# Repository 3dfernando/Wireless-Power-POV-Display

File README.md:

# Wireless-Power-POV-Display
This project was designed as a hobby acivity by a Mechanical Engineer. Therefore, it probably has a lot of problems from the Electrical Engineering point of view. If you think you can improve this project, please branch this Git and comment!

The project consists of a POV (Persistence of Vision) display that, unlike most of the POV displays found in the internet, is not powered by a battery but by the mains power. The regular battery-powered design is a simple solution to the problem of supplying the power needed to light up the LEDs and power the processor [Which are spinning], by making the battery also spin. 

Although the solution is effective, it's a hassle to be applied for a decorative item, for example, as one needs to stop and access the device from time to time to recharge the battery. Normally decorative objects have a no-maintenance requirement (which in some cases might be extremely difficult to achieve!).

The next easiest way of avoiding this problem is through a brushed connection. This is also possible, although it might be a little bit too noisy for a decorative device - and still would be hard for a DIY setup to require no maintenance after some hours of operation. So I thought a wireless power transfer system would be a perfect solution! So why not try it out and in the middle of the path learn more about wireless power transfer?

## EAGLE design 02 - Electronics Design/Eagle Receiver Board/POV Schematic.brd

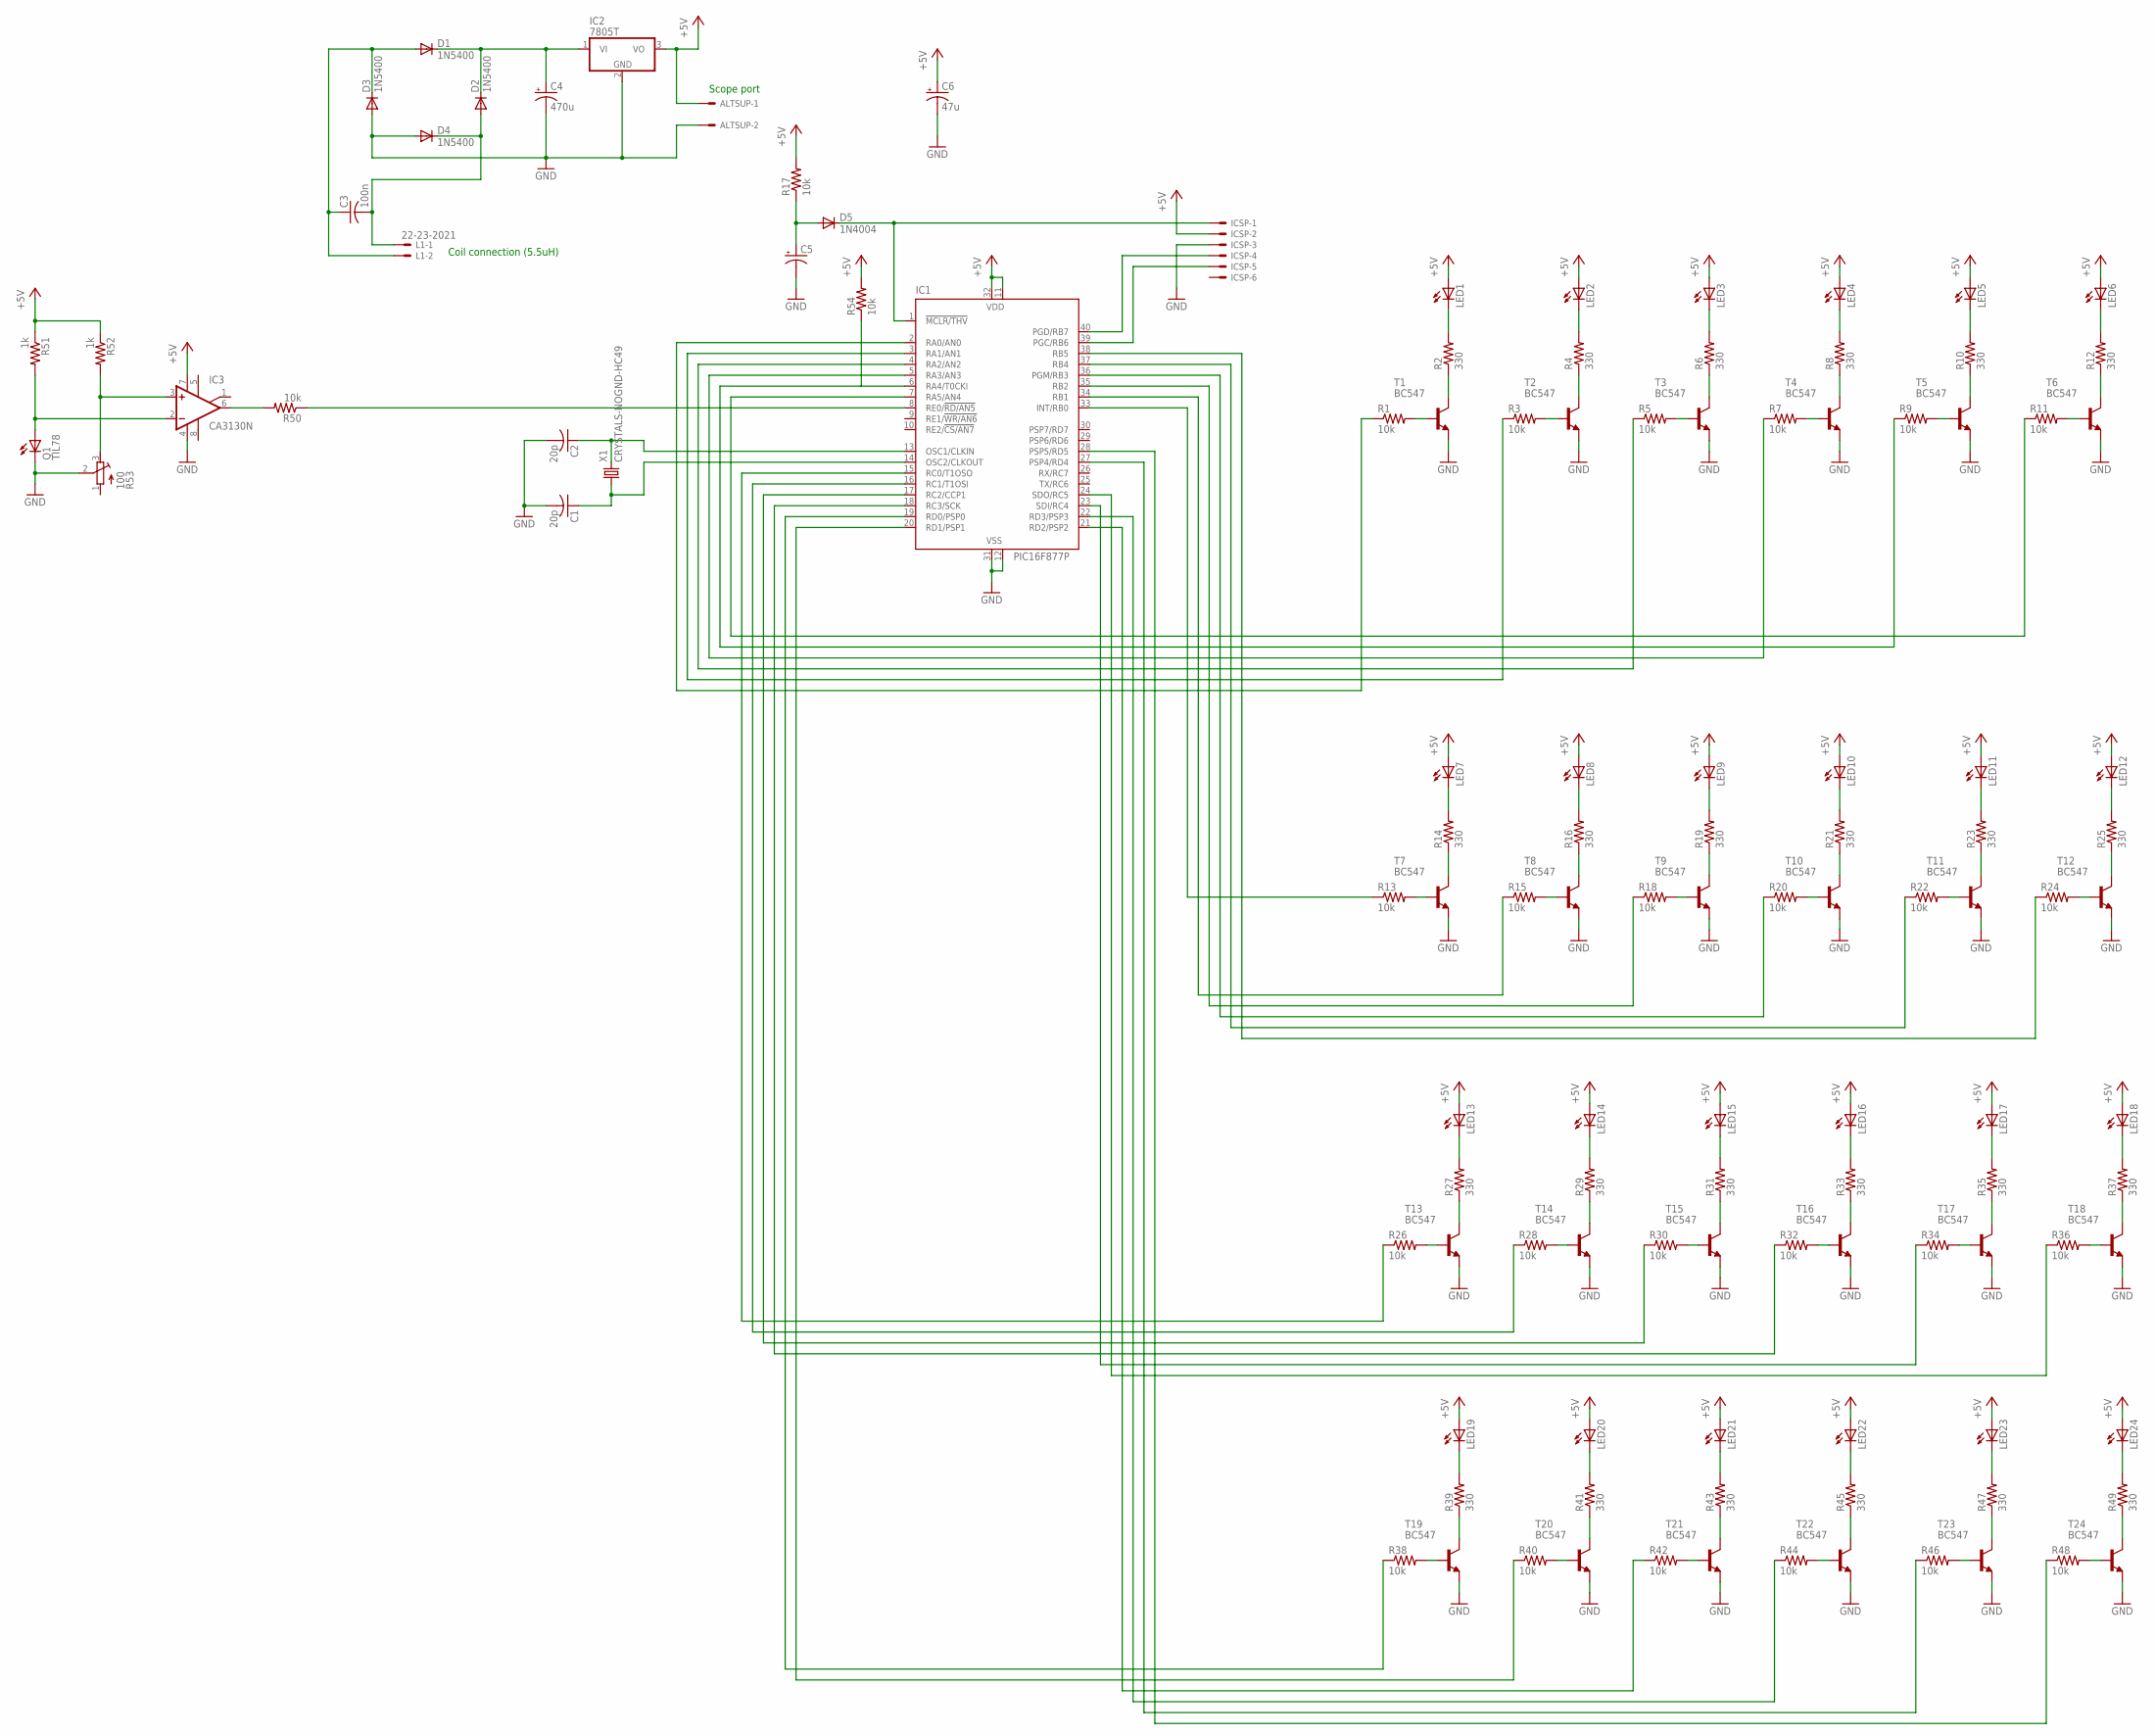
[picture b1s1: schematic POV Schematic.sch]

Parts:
ALTSUP: KK-156-2
C1, C2: 20p; C025-024X044
C3: 100n; C050-025X075
C4: 470u; E3,5-8
C5: CPOL-USE3.5-8; E3,5-8
C6: 47u; E3,5-8
D1, D2, D3, D4: 1N5400; DO201-15
D5: 1N4004; DO41-10
IC1: PIC16F877P; DIL40
IC2: 7805T; TO220H
IC3: CA3130N; DIL08
ICSP: KK-156-6
L1: 22-23-2021
LED1, LED2, LED3, LED4, LED5, LED6, LED7, LED8, LED9, LED10, LED11, LED12, LED13, LED14, LED15, LED16, LED17, LED18, LED19, LED20, LED21, LED22, LED23, LED24: LED5MM
Q1: TIL78; LED5MM
R1, R3, R5, R7, R9, R11, R13, R15, R17, R18, R20, R22, R24, R26, R28, R30, R32, R34, R36, R38, R40, R42, R44, R46, R48, R50, R54: 10k; 0204V
R2, R4, R6, R8, R10, R12, R14, R16, R19, R21, R23, R25, R27, R29, R31, R33, R35, R37, R39, R41, R43, R45, R47, R49: 330; 0204V
R51, R52: 1k; 0204V
R53: 100; RTRIM3296W
T1, T2, T3, T4, T5, T6, T7, T8, T9, T10, T11, T12, T13, T14, T15, T16, T17, T18, T19, T20, T21, T22, T23, T24: BC547; TO92
X1: CRYSTALS-NOGND-HC49; HC49

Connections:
+5V: ALTSUP.1, C6.+, IC1.11 (VDD), IC1.32 (VDD), IC2.3 (VO), IC3.7 (V+), ICSP.2, LED1.A, LED2.A, LED3.A, LED4.A, LED5.A, LED6.A, LED7.A, LED8.A, LED9.A, LED10.A, LED11.A, LED12.A, LED13.A, LED14.A, LED15.A, LED16.A, LED17.A, LED18.A, LED19.A, LED20.A, LED21.A, LED22.A, LED23.A, LED24.A, R17.2, R51.1, R52.1, R54.2
GND: ALTSUP.2, C1.2, C2.2, C4.-, C5.-, C6.-, D3.A, D4.A, IC1.12 (VSS), IC1.31 (VSS), IC2.2 (GND), IC3.4 (V-), ICSP.3, Q1.K (C), R53.2 (S), T1.1 (E), T2.1 (E), T3.1 (E), T4.1 (E), T5.1 (E), T6.1 (E), T7.1 (E), T8.1 (E), T9.1 (E), T10.1 (E), T11.1 (E), T12.1 (E), T13.1 (E), T14.1 (E), T15.1 (E), T16.1 (E), T17.1 (E), T18.1 (E), T19.1 (E), T20.1 (E), T21.1 (E), T22.1 (E), T23.1 (E), T24.1 (E)
unnamed: C3.2, D2.A, D4.C, L1.1
unnamed: C3.1, D1.A, D3.C, L1.2
unnamed: D5.C, IC1.1 (!MCLR/THV), ICSP.1
unnamed: C5.+, D5.A, R17.1
unnamed: C2.1, IC1.13 (OSC1/CLKIN), X1.2
unnamed: C4.+, D1.C, D2.C, IC2.1 (VI)
unnamed: C1.1, IC1.14 (OSC2/CLKOUT), X1.1
unnamed: R2.1, T1.3 (C)
unnamed: LED1.K (C), R2.2
unnamed: R1.2, T1.2 (B)
unnamed: R4.1, T2.3 (C)
unnamed: LED2.K (C), R4.2
unnamed: R3.2, T2.2 (B)
unnamed: R6.1, T3.3 (C)
unnamed: LED3.K (C), R6.2
unnamed: R5.2, T3.2 (B)
unnamed: R8.1, T4.3 (C)
unnamed: LED4.K (C), R8.2
unnamed: R7.2, T4.2 (B)
unnamed: R10.1, T5.3 (C)
unnamed: LED5.K (C), R10.2
unnamed: R9.2, T5.2 (B)
unnamed: R12.1, T6.3 (C)
unnamed: LED6.K (C), R12.2
unnamed: R11.2, T6.2 (B)
unnamed: R14.1, T7.3 (C)
unnamed: LED7.K (C), R14.2
unnamed: R13.2, T7.2 (B)
unnamed: R16.1, T8.3 (C)
unnamed: LED8.K (C), R16.2
unnamed: R15.2, T8.2 (B)
unnamed: R39.1, T19.3 (C)
unnamed: IC1.40 (PGD/RB7), ICSP.4
unnamed: IC1.39 (PGC/RB6), ICSP.5
unnamed: IC1.2 (RA0/AN0), R1.1
unnamed: IC1.3 (RA1/AN1), R3.1
unnamed: IC1.4 (RA2/AN2), R5.1
unnamed: IC1.5 (RA3/AN3), R7.1
unnamed: IC1.7 (RA5/AN4), R11.1
unnamed: R19.1, T9.3 (C)
unnamed: LED9.K (C), R19.2
unnamed: R18.2, T9.2 (B)
unnamed: R21.1, T10.3 (C)
unnamed: LED10.K (C), R21.2
unnamed: R20.2, T10.2 (B)
unnamed: R23.1, T11.3 (C)
unnamed: LED11.K (C), R23.2
unnamed: R22.2, T11.2 (B)
unnamed: R25.1, T12.3 (C)
unnamed: LED12.K (C), R25.2
unnamed: R24.2, T12.2 (B)
unnamed: IC1.33 (INT/RB0), R13.1
unnamed: IC1.34 (RB1), R15.1
unnamed: IC1.35 (RB2), R18.1
unnamed: IC1.36 (PGM/RB3), R20.1
unnamed: IC1.37 (RB4), R22.1
unnamed: IC1.38 (RB5), R24.1
unnamed: R27.1, T13.3 (C)
unnamed: LED13.K (C), R27.2
unnamed: R26.2, T13.2 (B)
unnamed: R29.1, T14.3 (C)
unnamed: LED14.K (C), R29.2
unnamed: R28.2, T14.2 (B)
unnamed: R31.1, T15.3 (C)
unnamed: LED15.K (C), R31.2
unnamed: R30.2, T15.2 (B)
unnamed: R33.1, T16.3 (C)
unnamed: LED16.K (C), R33.2
unnamed: R32.2, T16.2 (B)
unnamed: R35.1, T17.3 (C)
unnamed: LED17.K (C), R35.2
unnamed: R34.2, T17.2 (B)
unnamed: R37.1, T18.3 (C)
unnamed: LED18.K (C), R37.2
unnamed: R36.2, T18.2 (B)
unnamed: LED19.K (C), R39.2
unnamed: R38.2, T19.2 (B)
unnamed: R41.1, T20.3 (C)
unnamed: LED20.K (C), R41.2
unnamed: R40.2, T20.2 (B)
unnamed: R43.1, T21.3 (C)
unnamed: LED21.K (C), R43.2
unnamed: R42.2, T21.2 (B)
unnamed: R45.1, T22.3 (C)
unnamed: LED22.K (C), R45.2
unnamed: R44.2, T22.2 (B)
unnamed: R47.1, T23.3 (C)
unnamed: LED23.K (C), R47.2
unnamed: R46.2, T23.2 (B)
unnamed: R49.1, T24.3 (C)
unnamed: LED24.K (C), R49.2
unnamed: R48.2, T24.2 (B)
unnamed: IC1.15 (RC0/T1OSO), R26.1
unnamed: IC1.16 (RC1/T1OSI), R28.1
unnamed: IC1.17 (RC2/CCP1), R30.1
unnamed: IC1.18 (RC3/SCK), R32.1
unnamed: IC1.23 (SDI/RC4), R34.1
unnamed: IC1.24 (SDO/RC5), R36.1
unnamed: IC1.19 (RD0/PSP0), R38.1
unnamed: IC1.20 (RD1/PSP1), R40.1
unnamed: IC1.21 (RD2/PSP2), R42.1
unnamed: IC1.22 (RD3/PSP3), R44.1
unnamed: IC1.27 (PSP4/RD4), R46.1
unnamed: IC1.28 (PSP5/RD5), R48.1
unnamed: IC3.2 (-IN), Q1.A, R51.2
unnamed: IC3.6 (OUT), R50.2
unnamed: IC1.8 (RE0/!RD/AN5), R50.1
unnamed: IC3.3 (+IN), R52.2, R53.3 (E)
unnamed: IC1.6 (RA4/T0CKI), R54.1

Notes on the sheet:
Coil connection (5.5uH)
Scope port

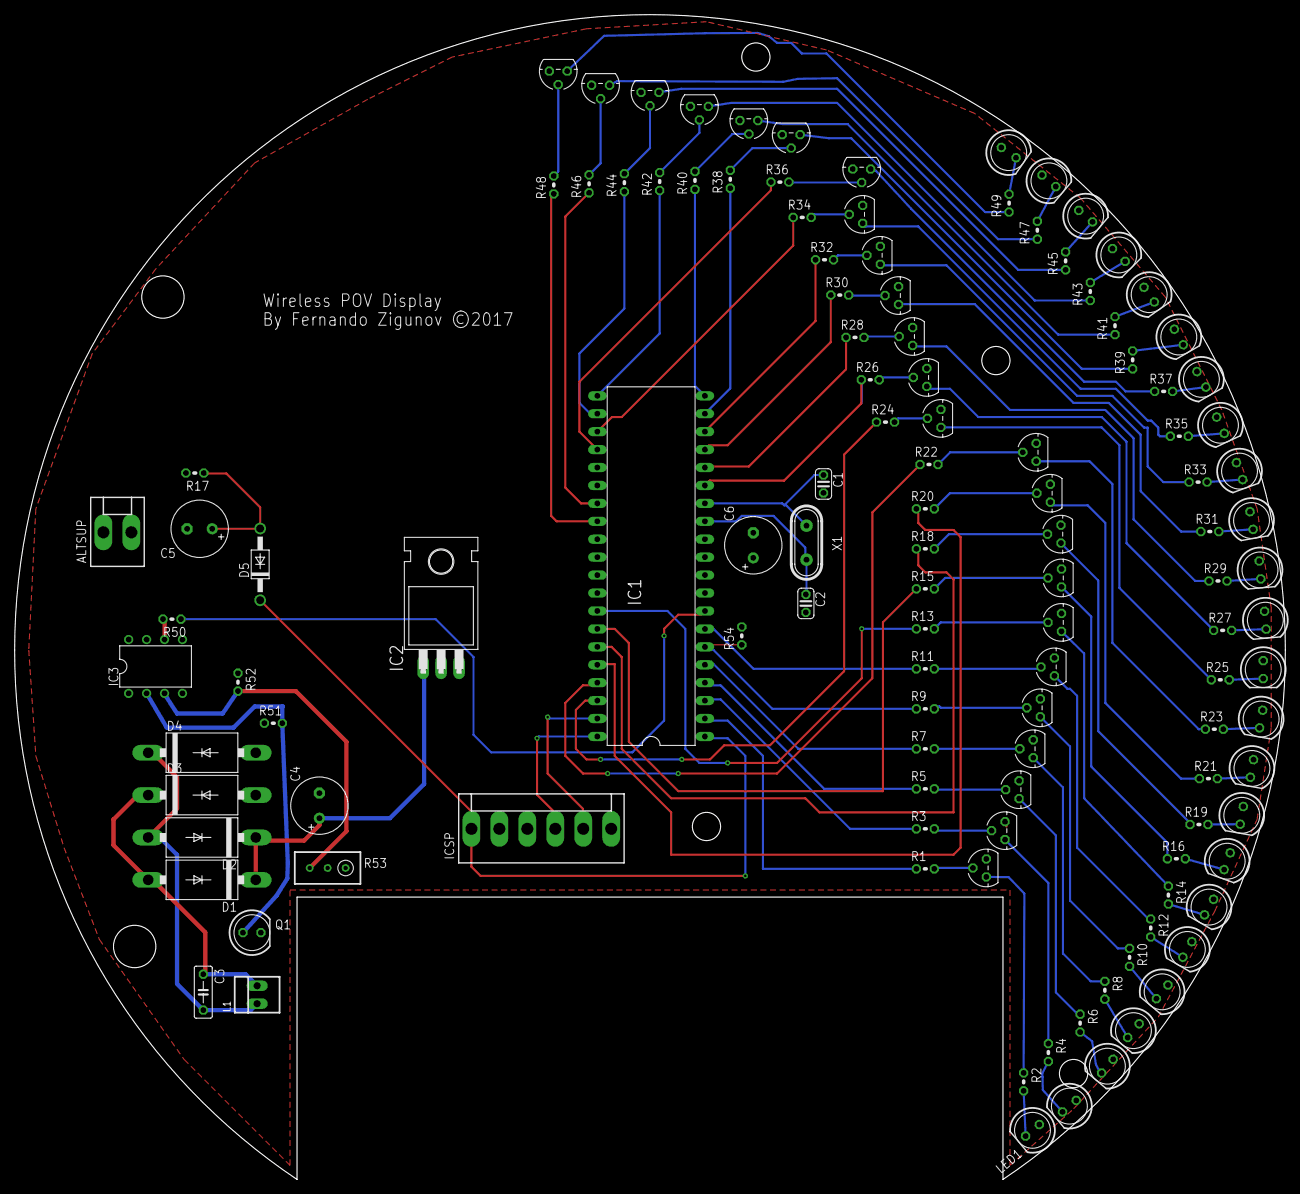
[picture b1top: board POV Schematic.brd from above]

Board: 2 copper layers, 180.0 x 165.0 mm, 121 parts (0 on the bottom side), 111 nets.

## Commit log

2017-02-24 Added resonant coupling device model in Matlab
2017-02-24 Create Fle
2017-02-24 Rename Resonant_Coupling_Circuit_Model.m to 02 - Electronics Design/Resonant_Coupling_Circuit_Model.m
2017-02-28 Added the wireless power transfer final circuit
2017-07-01 Uploaded the mechanical design
2017-07-01 Uploaded the electronics design files
2017-07-01 Added the programming files
2017-07-01 Uploaded the program for the PIC
2017-07-23 Used MPLab to compile the code
    >2k words available!

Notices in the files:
02 - Electronics Design/Eagle Receiver Board/POV Schematic.brd:
By Fernando Zigunov ©2017
